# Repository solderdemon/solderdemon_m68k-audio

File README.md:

# SolderDemon m68k Audio

## Overview

A SolderDemon m68k expansion card with three Yamaha YM2149F sound channels, noise and envelope generation, and passive stereo line output. An ATF22V10C sequencer handles bus timing for the PSG.

Designed for the SolderDemon m68k and compatible with the [rosco_m68k](https://github.com/rosco-m68k/rosco_m68k) expansion interface.

**Status.** r1 fabrication files are available. The current layout has yet to be tested on a physical board.

## Start here

- [KiCad project](design/solderdemon_m68k-audio.kicad_pro)
- [Schematic (PDF)](manufacturing/solderdemon_m68k-audio-schematic.pdf)
- [Assembly and bring-up](docs/BUILD.md)
- [Gerbers and drill files](manufacturing/solderdemon_m68k-audio-r1-2026-11-12-gerbers.zip)

## Board views

| Top | Bottom |
|:---:|:---:|
|  |  |

## Hardware

### Features

- **Sound Generator:** Yamaha **YM2149F** (`U1`, DIP-40): 3 tone channels (A, B, C), noise generator, and hardware envelope generator, clocked from a dedicated **1.8432 MHz 5 V oscillator** (`X1`, DIP-8).
- **Hardware-Timed Bus Interface:** The slow PSG never sees the fast MC68010 bus cycles directly. An intermediate octal latch (**CD74HCT273E**, `U2`) captures bus data (`D0`–`D7`), while an **ATF22V10C-15PU** PLD (`U3`) sequences `BDIR` strobes and asserts `~DTACK` when the write cycle finishes.
- **Address Decoding:** High-speed address decoding via **CD74HCT688E** (`U4`) magnitude comparator matching `A8`–`A15` against `$01`, combined with PLD qualification of `~IOSEL`, `~AS`, `~LDS`, `R/~W`, and `A16`–`A19` for the `$F00100`–`$F001FF` address block.
- **Zero Software Timing Loops:** Write cycles automatically insert CPU wait states until hardware asserts `~DTACK`. The CPU performs straightforward byte writes to register and data addresses at full speed without needing software delays or timers.
- **Bus Safety:** `BC1` is tied to GND and the hardware only accepts write cycles. Read cycles and PSG GPIO directions are physically excluded, eliminating any possibility of bus contention.
- **Passive ABC Stereo:** 1 kΩ channel loads and a resistive mixer: Channel A to left, Channel C to right, Channel B centered in both channels at −6.9 dB, followed by 10 µF AC coupling (`C7`/`C8`) and 100 kΩ DC bleeders.
- **Dual Outputs:** Front/side 3.5 mm TRS stereo jack **CUI SJ1-3525N** (`J2`) and an internal 1×3 vertical header (`J3`: L / GND / R) for case or mixer wiring.
- **Busboard Form Factor:** 100 × 72 mm 2-layer PCB with R4 mm corners. Plugs vertically into any 2×32 Eurocard bus slot (`J1`).
- **100% Through-Hole (THT):** All ICs socketed in standard DIP packages, axial/radial passive components for straightforward DIY assembly.

### Memory Map

The card is mapped into the SolderDemon m68k I/O region (`$F00000`–`$FFFFFF`), specifically claiming the 256-byte page `$F00100`–`$F001FF`. Because the YM2149 is an 8-bit peripheral wired to the lower data byte (`D0`–`D7`), all accesses must be byte writes with the Lower Data Strobe (`LDS`) asserted (odd addresses).

| Address | Mode | Function | Bus Lines |
|---|---|---|---|
| **`$F00101`** | Write-only (byte) | **PSG Register Address Latch** | `A1` = 0 (`BC2` = 0, `BDIR` pulsed high) |
| **`$F00103`** | Write-only (byte) | **PSG Data Value Write** | `A1` = 1 (`BC2` = 1, `BDIR` pulsed high) |
| **`$F00100`–`$F001FF`** | — | Mirrors of the above registers (`A2`–`A7` ignored) | Treat full `$F00100`–`$F001FF` page as occupied |

> **Note:** Only byte writes with `LDS` asserted are decoded and acknowledged. Word writes, long-word writes, upper-byte writes (`UDS`), and read cycles are ignored and will result in a CPU bus timeout / bus error if attempted.

#### Hardware-Timed Interface

The YM2149F bus control lines are `BDIR`, `BC1`, and `BC2`. This card ties `BC1` to ground, uses `BC2` driven by address line `A1`, and controls `BDIR` via the PLD sequencer:

| `BC2` (`A1`) | `BDIR` (PLD) | PSG Function |
|:---:|:---:|:---|
| `0` | `0` | Inactive |
| `0` | `1` | **Latch Register Address** (data from latch `U2` selected into address register) |
| `1` | `0` | Inactive |
| `1` | `1` | **Write Data to Register** (data from latch `U2` written to selected register) |

### Operating Principle

1. **Address Match & Qualification:** When the MC68010 initiates an I/O cycle with `~IOSEL`, `~AS`, `~LDS`, and write (`R/~W` low), `U4` (74HCT688) verifies that `A8`–`A15` equals `$01`. `U3` confirms that `A16`–`A19` are zero, asserting internal request `~NREQ`.
2. **Data Capture:** On the second sequencer clock (`S2`), `U3` generates a clock pulse to `U2` (`74HCT273`), latching the write data from bus lines `D0`–`D7`.
3. **Strobe Generation:** On state `S3`, `U3` asserts `BDIR` high to the PSG. It maintains `BDIR` asserted until state `S5`, providing a clean, jitter-free strobe of ~1.08 µs (well within the YM2149 requirement of 300 ns to 10 µs).
4. **Bus Cycle Acknowledgment:** On state `S6`, `U3` pulls the open-collector `~DTACK` line low, signaling to the CPU that the bus cycle is complete. The CPU terminates the write cycle and releases the bus.

## Using the board

### Programming Example

#### C Interface (`solderdemon_audio.h`)

```c
#include "solderdemon_audio.h"

void play_sound(void) {
    /* Set mixer: Tone A enabled, Noise disabled */
    sd_psg_write(7, 0x3E);

    /* Set Channel A period (e.g. middle C at 1.8432 MHz PSG clock) */
    sd_psg_write(0, 0xDC); /* Coarse */
    sd_psg_write(1, 0x01); /* Fine */

    /* Set Channel A volume to maximum (15) */
    sd_psg_write(8, 15);

    /* ... playback delay ... */

    /* Silence all voices */
    sd_psg_silence();
}
```

#### M68K Assembly (`demo.s`)

```asm
    .equ PSG_ADDR, 0x00f00101
    .equ PSG_DATA, 0x00f00103

/* D0.b = register 0..13, D1.b = value.
 * Disables interrupts during register/data pair write.
 */
psg_write:
    cmpi.b  #13,%d0
    bhi     3f
    move.w  %sr,-(%sp)
    ori.w   #0x0700,%sr     /* Inhibit interrupts */
    move.b  %d0,PSG_ADDR    /* Latch register number */
    move.b  %d1,PSG_DATA    /* Write register value */
    move.w  (%sp)+,%sr      /* Restore interrupt level */
3:  rts

psg_silence:
    movem.l %d0-%d1,-(%sp)
    moveq   #0,%d1
    moveq   #8,%d0
    bsr     psg_write       /* Volume A = 0 */
    moveq   #9,%d0
    bsr     psg_write       /* Volume B = 0 */
    moveq   #10,%d0
    bsr     psg_write       /* Volume C = 0 */
    movem.l (%sp)+,%d0-%d1
    rts
```

#### Building Code & PLD

```sh
# Assemble the test demo with m68k-elf toolchain
m68k-elf-gcc -m68000 -nostdlib -T code/software/demo/demo.ld code/software/demo/demo.s -o code/software/demo/demo.elf
m68k-elf-objcopy -O binary code/software/demo/demo.elf code/software/demo/demo.bin

# Compile PLD equations
galasm code/firmware/pld/audio_sequencer.pld
```

<!-- music-demo -->
### Musical demo: Korobeiniki (Tetris theme)

[`code/software/music_demo`](code/software/music_demo/README.md) contains a 30-second original
chiptune arrangement of the traditional Korobeiniki melody, familiar from Tetris.
It builds from solo to bass, arpeggios, stereo voice swap, and noise percussion.
Build with `rosco build --docker`; instructions and a WAV preview are included.
<!-- /music-demo -->

## Build and verification

### Bill of Materials (BOM)

| Reference | Value | Package / Footprint | Notes |
|---|---|---|---|
| **U1** | YM2149F | DIP-40, 15.24 mm (0.6") | Yamaha Sound Generator (PSG). Socket recommended. |
| **U2** | CD74HCT273E | DIP-20, 7.62 mm (0.3") | Octal D-type flip-flop with clear. Socket recommended. |
| **U3** | ATF22V10C-15PU | DIP-24, 7.62 mm (0.3") | PLD Write Sequencer / DTACK generator (-15 speed grade). |
| **U4** | CD74HCT688E | DIP-20, 7.62 mm (0.3") | 8-bit magnitude identity comparator. Socket recommended. |
| **X1** | 1.8432 MHz / 5V | DIP-8 (half-can) | Dedicated 5V crystal oscillator module (50 ppm). |
| **J1** | 2×32 Pin Socket | 2.54 mm, R/A Horizontal | Eurocard backplane connector. |
| **J2** | SJ1-3525N | 3.5 mm TRS Jack, Horizontal | CUI Devices horizontal stereo audio jack. |
| **J3** | 1×03 Pin Header | 2.54 mm, Vertical | Line out header: Pin 1 = Left, Pin 2 = GND, Pin 3 = Right. |
| **R1, R2** | 33 Ω | Axial DIN0207, P7.62 mm | Series damping resistors for clock lines. |
| **R3, R4** | 10 kΩ | Axial DIN0207, P7.62 mm | Logic pull-up resistors. |
| **R5–R7** | 1 kΩ | Axial DIN0207, P7.62 mm | PSG audio channel A/B/C load resistors (1% preferred). |
| **R8, R11** | 10 kΩ | Axial DIN0207, P7.62 mm | Channel A → Left, Channel C → Right mixer resistors. |
| **R9, R10** | 22 kΩ | Axial DIN0207, P7.62 mm | Channel B → Left & Right center mix (−6.9 dB). |
| **R12, R13** | 100 kΩ | Axial DIN0207, P7.62 mm | Output DC bleeder resistors. |
| **C1–C5** | 100 nF | Radial, 5.08 mm pitch | Decoupling capacitors (one per IC and oscillator). |
| **C6** | 47 µF / 16V | Radial D6.3 mm, P2.5 mm | Bulk electrolytic reservoir capacitor near bus power pins. |
| **C7, C8** | 10 µF / 16V | Radial D6.3 mm, P2.5 mm | AC coupling electrolytic capacitors (+ terminal toward mixer). |

> **Height & Sockets:** Use low-profile DIP sockets (one DIP-40, one DIP-24, two DIP-20, one DIP-8) and low-profile radial capacitors to ensure clearance within the standard 20.32 mm (0.8") Eurocard backplane slot pitch.

### Timing Budget & Sequencer States

Clocked by the 1.8432 MHz oscillator ($T_{clk} \approx 542.5\text{ ns}$), the ATF22V10C sequencer (`S0`–`S6`) executes the following cycle:

```text
State:    Idle    S0      S1      S2      S3      S4      S5      S6     Idle
Clock:    __|~~~|___|~~~|___|~~~|___|~~~|___|~~~|___|~~~|___|~~~|___|~~~|___|~~~
~NREQ:    ~~~~~~\________________________________________________/~~~~~~~~~~~
U2 Latch: ------------------------| LATCH |-----------------------------------
BDIR:     ________________________________|~~~~~~~~~~~~~~~~~~~~~~~|___________
~DTACK:   ~~~~~~~~~~~~~~~~~~~~~~~~~~~~~~~~~~~~~~~~~~~~~~~~~~~~~~~~|_______|~~~
```

- **Setup Time ($S_0 \to S_2$):** Data setup prior to strobe assertion is $\ge 414.5\text{ ns}$ (datasheet requires $\ge 300\text{ ns}$).
- **Strobe Width ($S_3 \to S_5$):** `BDIR` is asserted for 2 full clock cycles ($1005.0\text{ ns}$ to $1165.1\text{ ns}$), well within the Yamaha spec ($300\text{ ns} \le t_W \le 10000\text{ ns}$).
- **Hold Time ($S_5 \to S_6$):** Post-strobe data and address hold time is $\ge 444.5\text{ ns}$ (datasheet requires $\ge 80\text{ ns}$).
- **DTACK Assertion ($S_6$):** `DTACK` asserts on state `S6`. The CPU samples `DTACK` and terminates the bus cycle, safely causing `~NREQ` to deassert and resetting the sequencer asynchronously (`AR = NREQ`).

### PLD Firmware (U3)

The write sequencer logic is defined in [`code/firmware/pld/audio_sequencer.pld`](code/firmware/pld/audio_sequencer.pld) (GALasm) and pre-assembled into `code/firmware/pld/audio_sequencer.jed`:

```text
/NREQ = /IOSEL * /MATCH * /AS * /LDS * /RW * RESET * /A16 * /A17 * /A18 * /A19
AR = NREQ
S0.R = /NREQ
S1.R = S0
S2.R = S1
S3.R = S2
S4.R = S3
S5.R = S4
S6.R = S5
BDIR = S3 * /S5 * /NREQ
DTACK.T = GND
DTACK.E = S6 * /NREQ
```

#### Programming the ATF22V10C

Select **ATF22V10C** in your programmer and load [audio_sequencer.jed](code/firmware/pld/audio_sequencer.jed). With a TL866II+ or T48 and `minipro`:

```sh
minipro -p ATF22V10C -w code/firmware/pld/audio_sequencer.jed
```

### First Power-Up & Testing

1. **Visual & Continuity Inspection:**
   - Verify polarity of electrolytic capacitors `C6`, `C7`, and `C8` (`+` marks).
   - Verify notch and Pin 1 orientation for all IC sockets (`U1`–`U4`) and oscillator `X1`.
   - With ICs unpopulated, plug into a powered-off backplane and verify +5 V on power pins and 0 Ω to GND on ground pins. Ensure no VCC-to-GND shorts exist.
2. **PLD & Clock Verification:**
   - Insert `X1` and `U3` (programmed ATF22V10C). Power on the board.
   - Probe `U1` pin 22 (`PSGCLK`) with an oscilloscope to confirm a clean 1.8432 MHz square wave.
3. **Logic & PSG Installation:**
   - Power off, install `U4` (74HCT688), `U2` (74HCT273), and `U1` (YM2149F).
   - Connect active/powered speakers or an amplifier line input to `J2` (3.5 mm jack). **Do not connect passive speakers or low-impedance headphones directly** (this is a line-level output).
4. **Running the Demo:**
   - Load `code/software/demo/demo.bin` into memory at `0x00040000` via the SolderDemon m68k serial bootloader.
   - Execute the code. You should hear a clear C-major triad played across channels A, B, and C for approximately 1 second, followed by clean silence.
   - Verify with an oscilloscope that `BDIR` (`U1` pin 27) and `~DTACK` (`U3` pin 14) pulse during each register access.

### Design files

- **KiCad Project:** `design/solderdemon_m68k-audio.kicad_pro`, `design/solderdemon_m68k-audio.kicad_sch`, `design/solderdemon_m68k-audio.kicad_pcb` (KiCad 8/9/10 format)
- **Symbol Library:** `SolderDemonAudio.kicad_sym`
- **Schematic PDF:** [`solderdemon_m68k-audio.pdf`](solderdemon_m68k-audio.pdf)
- **Bill of Materials:** [`BOM.csv`](design/BOM.csv)
- **Automated Verification:**
  - `python tools/verify_design.py`: Full pin connectivity, 65,536 address pages, JEDEC fuse validation.
  - `tools/verify_demo.c`: Musashi MC68010 execution test validating 40 atomic MMIO writes and register preservation.

### Sources & References

- [Yamaha YM2149 Programmable Sound Generator Datasheet](docs/reference/ym2149.pdf)
- [Microchip ATF22V10C High-Performance EE PLD Datasheet](docs/reference/atf22v10c.pdf)
- [Texas Instruments CD74HCT273 Octal D-Type Flip-Flop Datasheet](docs/reference/cd74hct273.pdf)
- [Texas Instruments CD74HCT688 8-Bit Magnitude Comparator Datasheet](docs/reference/cd74hct688.pdf)

<!-- repository-layout -->
## Repository layout

- [`design/`](design/solderdemon_m68k-audio.kicad_pro): KiCad project, schematic sheets, PCB, local libraries and design data. Open the project directly here.
- [`code/firmware/`](code/firmware/): ROM and programmable-logic sources and programming files.
- [`code/software/`](code/software/): drivers, examples and applications.
- [`code/build/`](code/build/): local build products; ignored by Git except for its README.
- [`tools/`](tools/): generators, simulations and export scripts. Run commands from the repository root unless stated otherwise.
- [`manufacturing/`](manufacturing/): fabrication packages.

Programmable-logic files are in `code/firmware/pld/`. Native CPLD tools retain their adjacent `bin/` outputs.
Design files and documentation are generated by scripts in `tools/`; change the sources and regenerate. Keep `.kicad_pro` as the source of DRC rules. The KiCad project includes the custom footprints required to inspect the board independently. Full regeneration and routing additionally require the shared workspace tools; see [the build guide](docs/BUILD.md).
<!-- /repository-layout -->

## Licences and attribution

Copyright © 2026 SolderDemon.

- **Hardware** — [CERN Open Hardware Licence v1.2](LICENCE.hardware.txt).
- **Code** — [MIT](LICENSE.code) for the sequencer PLD, driver, demos and verification tools.

Third-party materials retain their original notices and licence terms.

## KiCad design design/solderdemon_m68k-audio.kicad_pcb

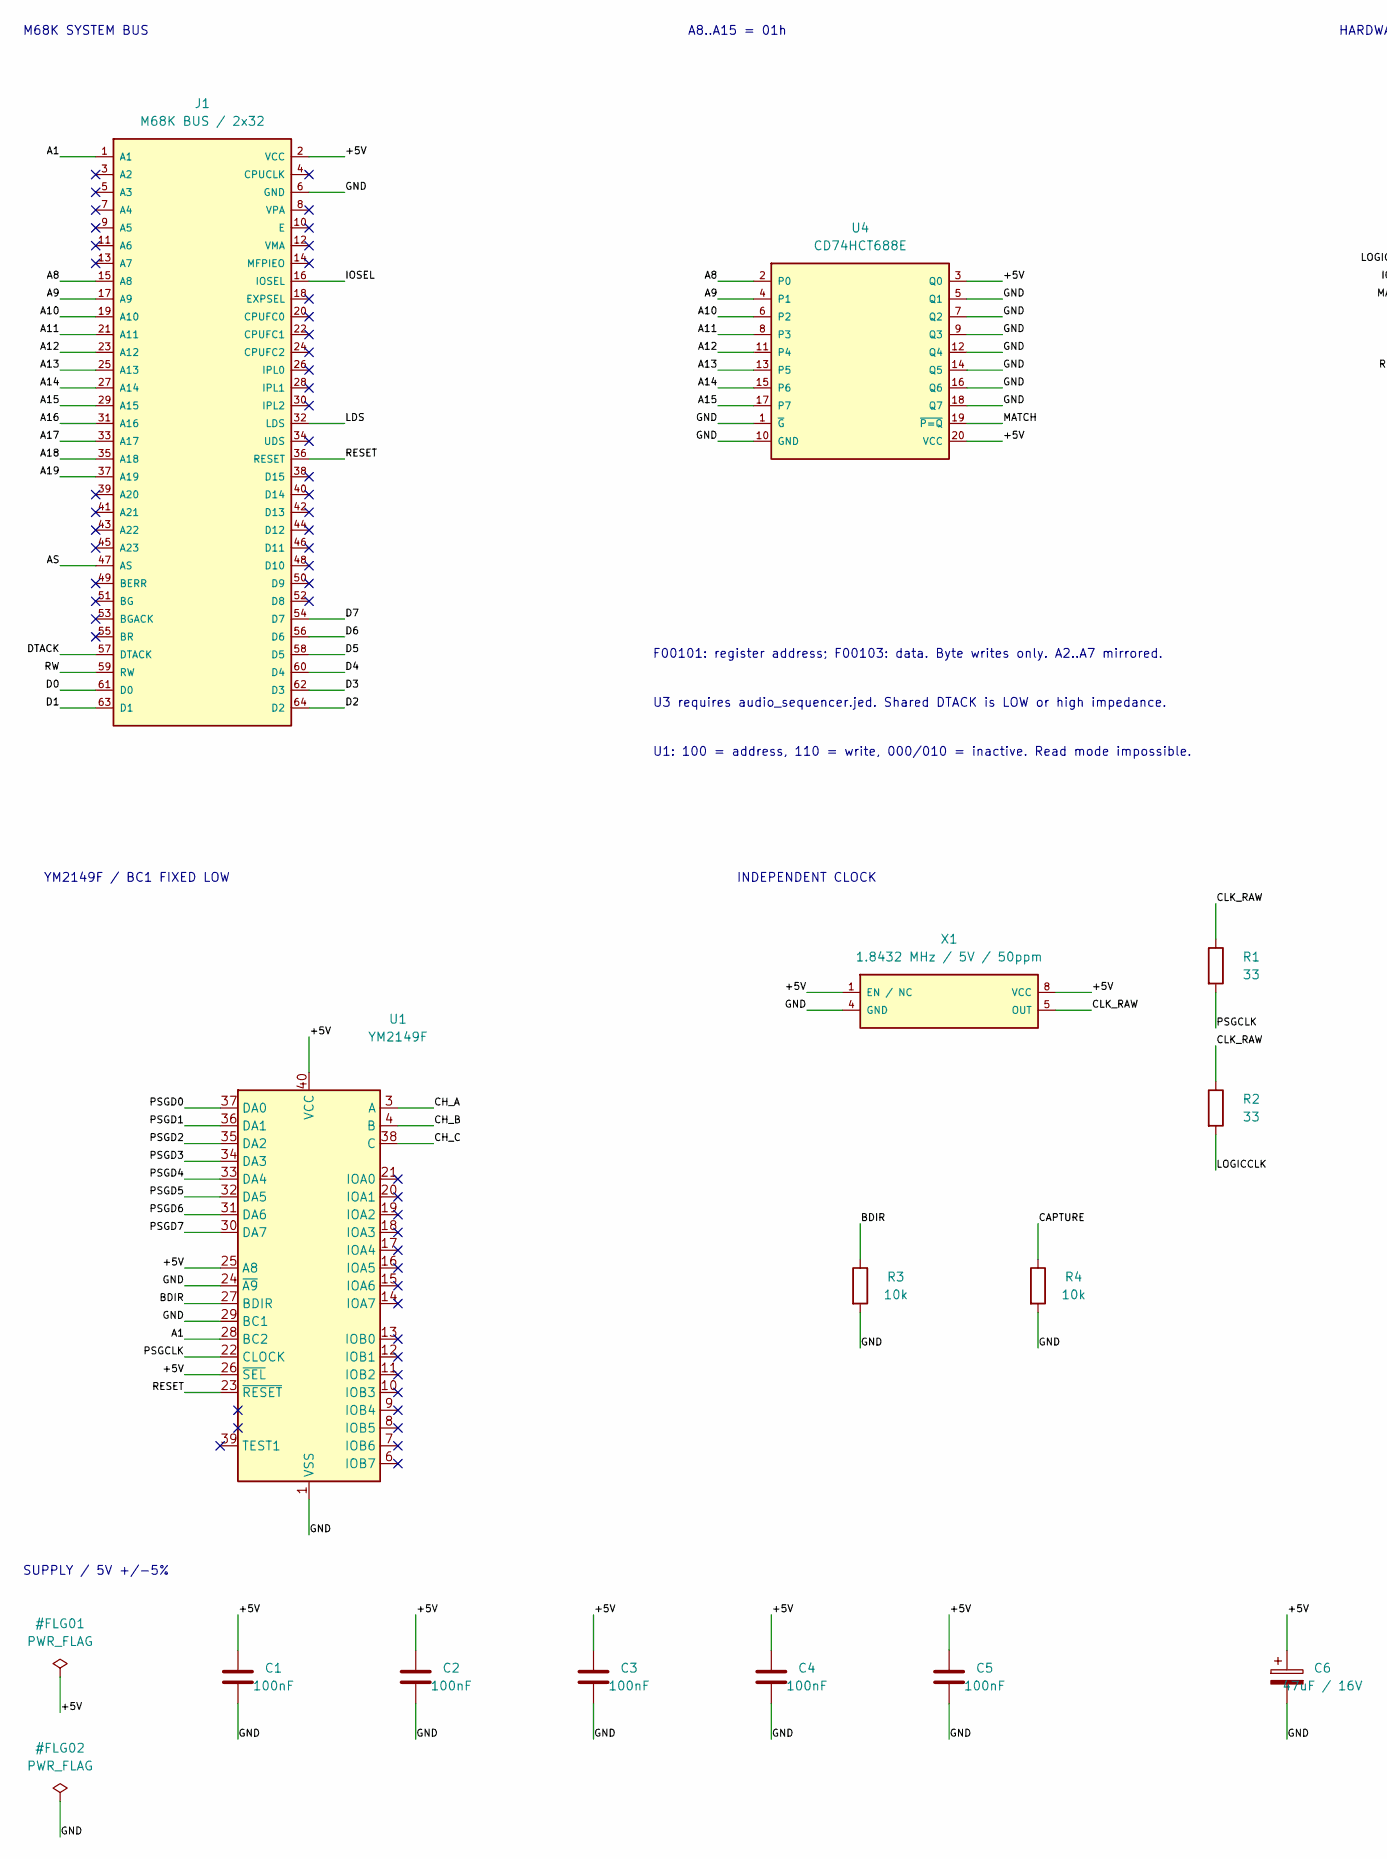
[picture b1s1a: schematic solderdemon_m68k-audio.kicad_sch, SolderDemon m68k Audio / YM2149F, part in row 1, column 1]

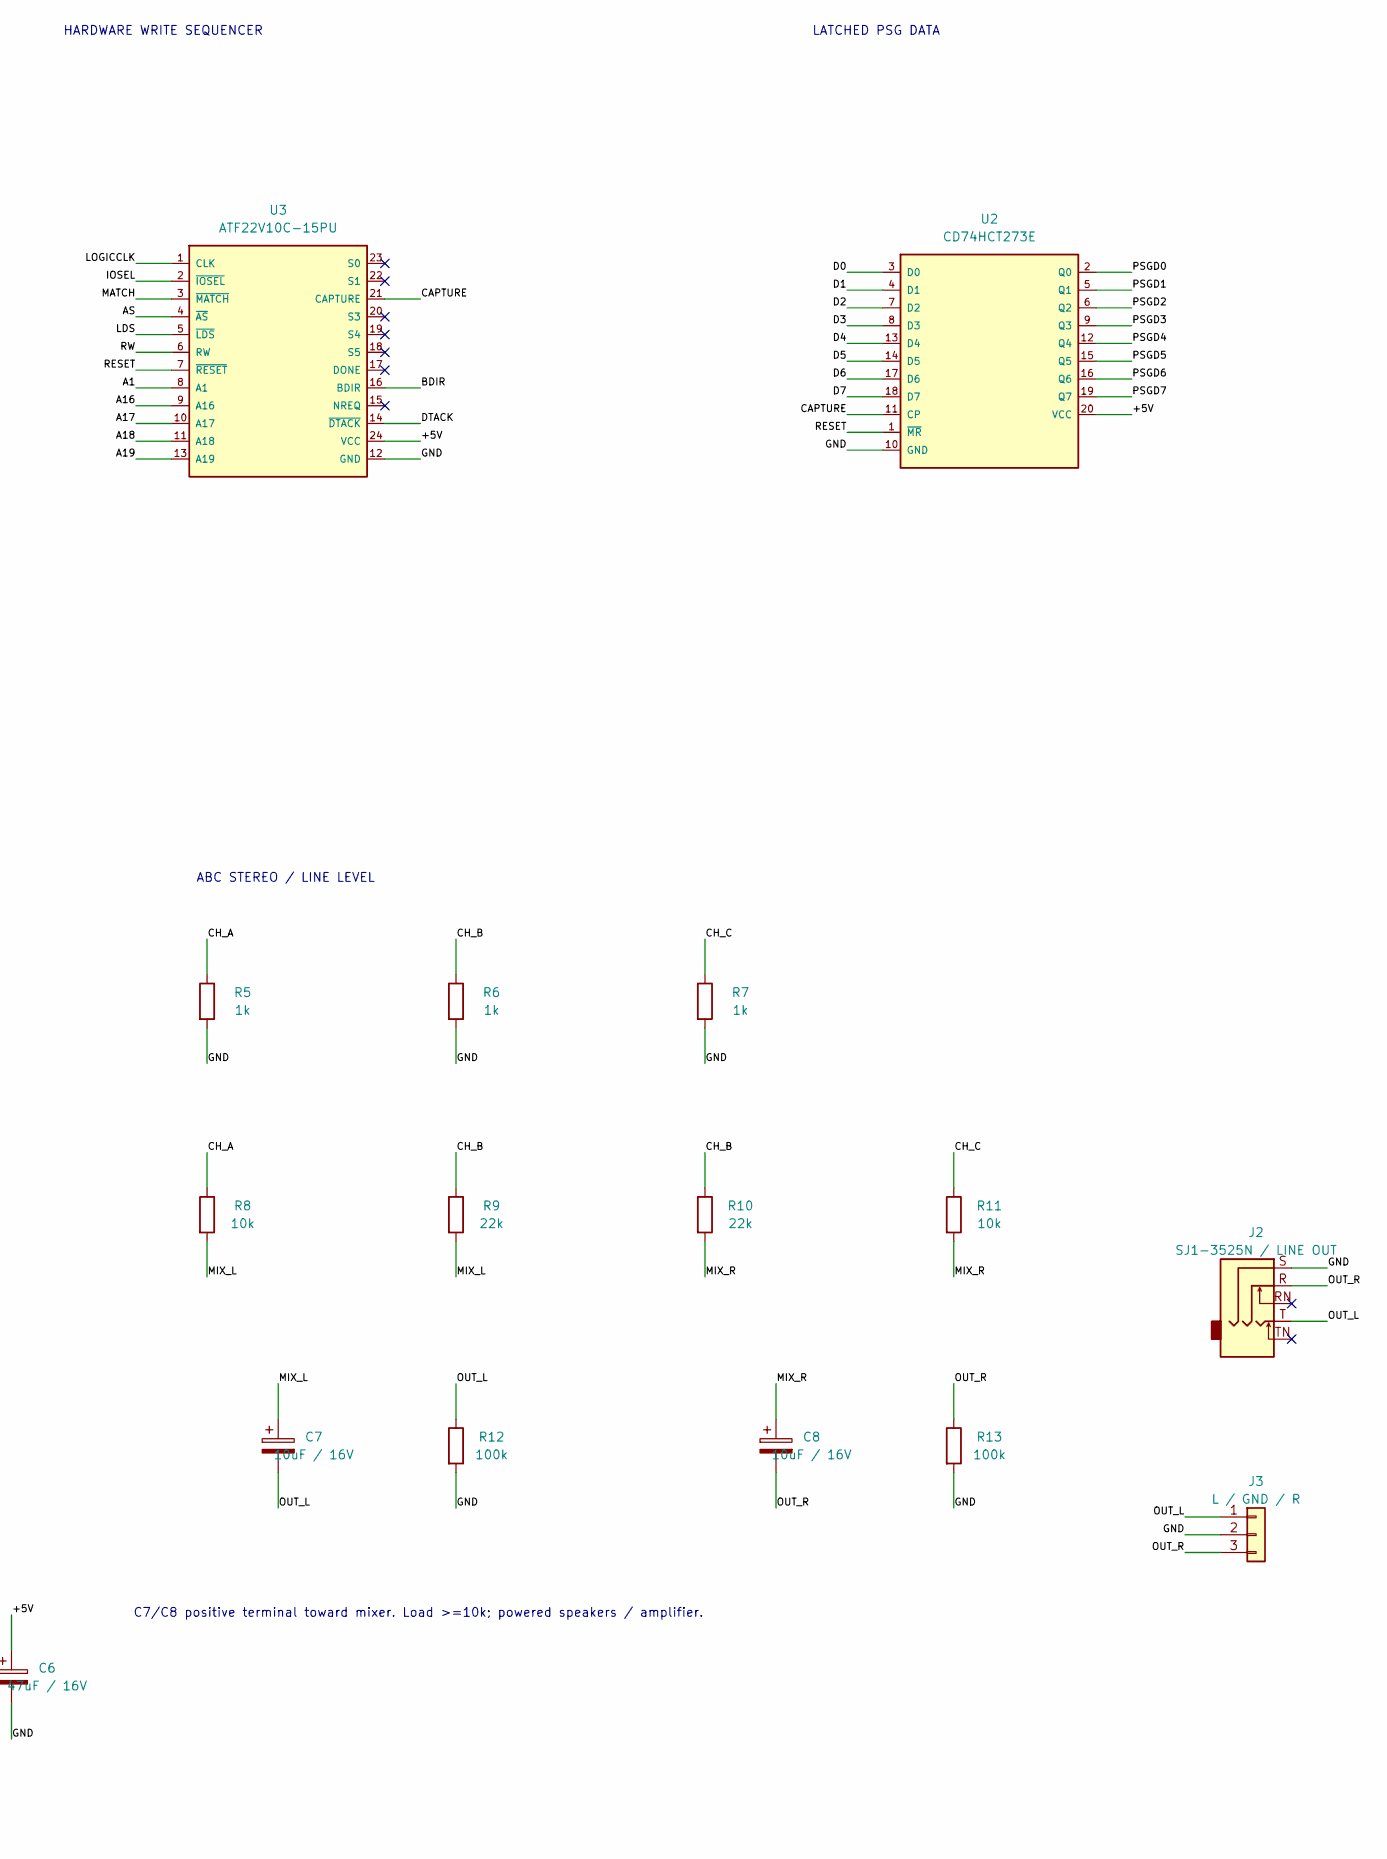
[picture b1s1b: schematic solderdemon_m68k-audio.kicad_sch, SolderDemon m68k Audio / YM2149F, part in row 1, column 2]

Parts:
C1, C2, C3, C4, C5: 100nF; C_Radial_5.08mm
C6: 47uF / 16V; CP_Radial_D6.3mm_P2.50mm
C7, C8: 10uF / 16V; CP_Radial_D6.3mm_P2.50mm
J1: M68K BUS / 2x32; PinSocket_2x32_P2.54mm_Horizontal_EdgeMount
J2: SJ1-3525N / LINE OUT; Jack_3.5mm_CUI_SJ1-3525N_Horizontal_EdgeMount
J3: L / GND / R; PinHeader_1x03_P2.54mm_Vertical
R1, R2: 33; R_Axial_DIN0207_L6.3mm_D2.5mm_P7.62mm_Horizontal
R3, R4, R8, R11: 10k; R_Axial_DIN0207_L6.3mm_D2.5mm_P7.62mm_Horizontal
R5, R6, R7: 1k; R_Axial_DIN0207_L6.3mm_D2.5mm_P7.62mm_Horizontal
R9, R10: 22k; R_Axial_DIN0207_L6.3mm_D2.5mm_P7.62mm_Horizontal
R12, R13: 100k; R_Axial_DIN0207_L6.3mm_D2.5mm_P7.62mm_Horizontal
U1: YM2149F; DIP-40_W15.24mm_Socket_LongPads
U2: CD74HCT273E; DIP-20_W7.62mm_Socket_LongPads
U3: ATF22V10C-15PU; DIP-24_W7.62mm_Socket_LongPads
U4: CD74HCT688E; DIP-20_W7.62mm_Socket_LongPads
X1: 1.8432 MHz / 5V / 50ppm; Oscillator_DIP-8

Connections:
/+5V: C1.1, C2.1, C3.1, C4.1, C5.1, C6.1, J1.2 (VCC), U1.25 (A8), U1.26 (~SEL), U1.40 (VCC), U2.20 (VCC), U3.24 (VCC), U4.3 (Q0), U4.20 (VCC), X1.1 (EN_/_NC), X1.8 (VCC)
/A1: J1.1 (A1), U1.28 (BC2), U3.8 (A1)
/A8: J1.15 (A8), U4.2 (P0)
/A9: J1.17 (A9), U4.4 (P1)
/A10: J1.19 (A10), U4.6 (P2)
/A11: J1.21 (A11), U4.8 (P3)
/A12: J1.23 (A12), U4.11 (P4)
/A13: J1.25 (A13), U4.13 (P5)
/A14: J1.27 (A14), U4.15 (P6)
/A15: J1.29 (A15), U4.17 (P7)
/A16: J1.31 (A16), U3.9 (A16)
/A17: J1.33 (A17), U3.10 (A17)
/A18: J1.35 (A18), U3.11 (A18)
/A19: J1.37 (A19), U3.13 (A19)
/AS: J1.47 (AS), U3.4 (~AS)
/BDIR: R3.1, U1.27 (BDIR), U3.16 (BDIR)
/CAPTURE: R4.1, U2.11 (CP), U3.21 (CAPTURE)
/CH_A: R5.1, R8.1, U1.3 (A)
/CH_B: R6.1, R9.1, R10.1, U1.4 (B)
/CH_C: R7.1, R11.1, U1.38 (C)
/CLK_RAW: R1.1, R2.1, X1.5 (OUT)
/D0: J1.61 (D0), U2.3 (D0)
/D1: J1.63 (D1), U2.4 (D1)
/D2: J1.64 (D2), U2.7 (D2)
/D3: J1.62 (D3), U2.8 (D3)
/D4: J1.60 (D4), U2.13 (D4)
/D5: J1.58 (D5), U2.14 (D5)
/D6: J1.56 (D6), U2.17 (D6)
/D7: J1.54 (D7), U2.18 (D7)
/DTACK: J1.57 (DTACK), U3.14 (~DTACK)
/GND: C1.2, C2.2, C3.2, C4.2, C5.2, C6.2, J1.6 (GND), J2.S, J3.2, R3.2, R4.2, R5.2, R6.2, R7.2, R12.2, R13.2, U1.1 (VSS), U1.24 (~A9), U1.29 (BC1), U2.10 (GND), U3.12 (GND), U4.1 (~G), U4.5 (Q1), U4.7 (Q2), U4.9 (Q3), U4.10 (GND), U4.12 (Q4), U4.14 (Q5), U4.16 (Q6), U4.18 (Q7), X1.4 (GND)
/IOSEL: J1.16 (IOSEL), U3.2 (~IOSEL)
/LDS: J1.32 (LDS), U3.5 (~LDS)
/LOGICCLK: R2.2, U3.1 (CLK)
/MATCH: U3.3 (~MATCH), U4.19 (~P=Q)
/MIX_L: C7.1, R8.2, R9.2
/MIX_R: C8.1, R10.2, R11.2
/OUT_L: C7.2, J2.T, J3.1, R12.1
/OUT_R: C8.2, J2.R, J3.3, R13.1
/PSGCLK: R1.2, U1.22 (CLOCK)
/PSGD0: U1.37 (DA0), U2.2 (Q0)
/PSGD1: U1.36 (DA1), U2.5 (Q1)
/PSGD2: U1.35 (DA2), U2.6 (Q2)
/PSGD3: U1.34 (DA3), U2.9 (Q3)
/PSGD4: U1.33 (DA4), U2.12 (Q4)
/PSGD5: U1.32 (DA5), U2.15 (Q5)
/PSGD6: U1.31 (DA6), U2.16 (Q6)
/PSGD7: U1.30 (DA7), U2.19 (Q7)
/RESET: J1.36 (RESET), U1.23 (~RESET), U2.1 (~MR), U3.7 (~RESET)
/RW: J1.59 (RW), U3.6 (RW)

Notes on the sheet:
M68K SYSTEM BUS
A8..A15 = 01h
HARDWARE WRITE SEQUENCER
LATCHED PSG DATA
YM2149F / BC1 FIXED LOW
INDEPENDENT CLOCK
ABC STEREO / LINE LEVEL
SUPPLY / 5V +/-5%
F00101: register address; F00103: data. Byte writes only. A2..A7 mirrored.
U3 requires audio_sequencer.jed. Shared DTACK is LOW or high impedance.
U1: 100 = address, 110 = write, 000/010 = inactive. Read mode impossible.
C7/C8 positive terminal toward mixer. Load >=10k; powered speakers / amplifier.

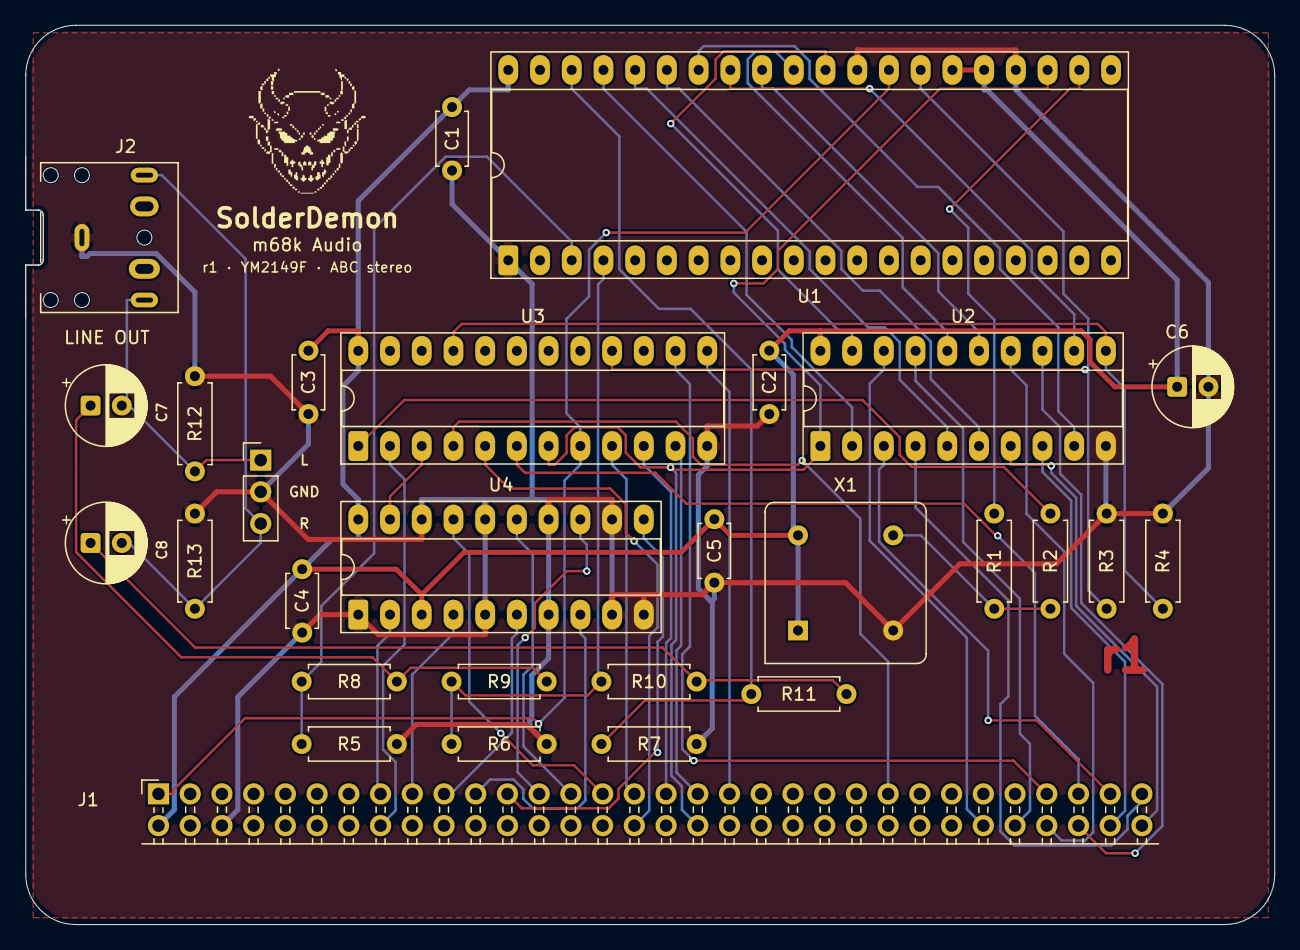
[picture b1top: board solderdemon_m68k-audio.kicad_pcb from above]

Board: 2 copper layers, 100.0 x 72.0 mm, 30 parts (0 on the bottom side), 50 nets.

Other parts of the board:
LOGO1: SolderDemon_Logo

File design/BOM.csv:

Reference,Value,Footprint
J1,M68K BUS / 2x32,SolderDemonAudio:PinSocket_2x32_P2.54mm_Horizontal_EdgeMount
U4,CD74HCT688E,Package_DIP:DIP-20_W7.62mm_Socket_LongPads
U3,ATF22V10C-15PU,Package_DIP:DIP-24_W7.62mm_Socket_LongPads
U2,CD74HCT273E,Package_DIP:DIP-20_W7.62mm_Socket_LongPads
U1,YM2149F,Package_DIP:DIP-40_W15.24mm_Socket_LongPads
X1,1.8432 MHz / 5V / 50ppm,Oscillator:Oscillator_DIP-8
R1,33,Resistor_THT:R_Axial_DIN0207_L6.3mm_D2.5mm_P7.62mm_Horizontal
R2,33,Resistor_THT:R_Axial_DIN0207_L6.3mm_D2.5mm_P7.62mm_Horizontal
R3,10k,Resistor_THT:R_Axial_DIN0207_L6.3mm_D2.5mm_P7.62mm_Horizontal
R4,10k,Resistor_THT:R_Axial_DIN0207_L6.3mm_D2.5mm_P7.62mm_Horizontal
C1,100nF,SolderDemonCaps:C_Radial_5.08mm
C2,100nF,SolderDemonCaps:C_Radial_5.08mm
C3,100nF,SolderDemonCaps:C_Radial_5.08mm
C4,100nF,SolderDemonCaps:C_Radial_5.08mm
C5,100nF,SolderDemonCaps:C_Radial_5.08mm
C6,47uF / 16V,Capacitor_THT:CP_Radial_D6.3mm_P2.50mm
R5,1k,Resistor_THT:R_Axial_DIN0207_L6.3mm_D2.5mm_P7.62mm_Horizontal
R6,1k,Resistor_THT:R_Axial_DIN0207_L6.3mm_D2.5mm_P7.62mm_Horizontal
R7,1k,Resistor_THT:R_Axial_DIN0207_L6.3mm_D2.5mm_P7.62mm_Horizontal
R8,10k,Resistor_THT:R_Axial_DIN0207_L6.3mm_D2.5mm_P7.62mm_Horizontal
R9,22k,Resistor_THT:R_Axial_DIN0207_L6.3mm_D2.5mm_P7.62mm_Horizontal
R10,22k,Resistor_THT:R_Axial_DIN0207_L6.3mm_D2.5mm_P7.62mm_Horizontal
R11,10k,Resistor_THT:R_Axial_DIN0207_L6.3mm_D2.5mm_P7.62mm_Horizontal
C7,10uF / 16V,Capacitor_THT:CP_Radial_D6.3mm_P2.50mm
C8,10uF / 16V,Capacitor_THT:CP_Radial_D6.3mm_P2.50mm
R12,100k,Resistor_THT:R_Axial_DIN0207_L6.3mm_D2.5mm_P7.62mm_Horizontal
R13,100k,Resistor_THT:R_Axial_DIN0207_L6.3mm_D2.5mm_P7.62mm_Horizontal
J2,SJ1-3525N / LINE OUT,SolderDemonAudio:Jack_3.5mm_CUI_SJ1-3525N_Horizontal_EdgeMount
J3,L / GND / R,Connector_PinHeader_2.54mm:PinHeader_1x03_P2.54mm_Vertical
